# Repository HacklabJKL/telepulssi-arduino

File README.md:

<!-- -*- mode: markdown; -*- -->
# Telepulssi TP-KN10 driver for Arduino

Local radio amateur club OH6AD has "bonked" some 80s display modules
built by Telepulssi Oy. [Zouppen](https://twitter.com/zouppen) and
kahvikello accepted the challenge of reverse engineering them to
display animations via USB and developed this driver.

See [Youtube video](https://www.youtube.com/watch?v=fZEshGM8jz8) of
the screen in action.

## Building

Open Arduino IDE and build [avr.ino](avr/avr.ino). Supported
microcontrollers include all ATMega328 and ATMega32u4 models. Can
easily ported to other MCUs. Change pin definitions in the source if
your hardware is different from ours.

To see how to wire TP-KN10 to Arduino, see [pinout](pinout.md).

## Processing

[Processing](https://processing.org/) is the most fun way to control
Telepulssi. Processing version 3.3 or newer is recommended.

Open
[processing/hello/hello.pde](processing/hello/hello.pde)
to Processing, change serial port name, hack and run! :-)

Also, it has Telepulssi emulator!

## UDP interface

When running UDP interface, first set serial port settings (replace
serial port to match yours):

```sh
stty -F /dev/ttyACM0 raw 19200
```

### Start UDP server

```sh
cd tools
runghc UdpServer.hs >/dev/ttyACM0
```

TODO: Make Cabal package for UdpServer to make it run more easily.

### Send PNG images

Send any image over UDP port to this screen by running:

```sh
nc -uw0 SERVER_IP 1337 <your_image.png
```

### Naïve clock

```sh
./effects/clock /dev/ttyUSB0
```

## Missing features

1. Cabal package for UDP server
1. Schematics

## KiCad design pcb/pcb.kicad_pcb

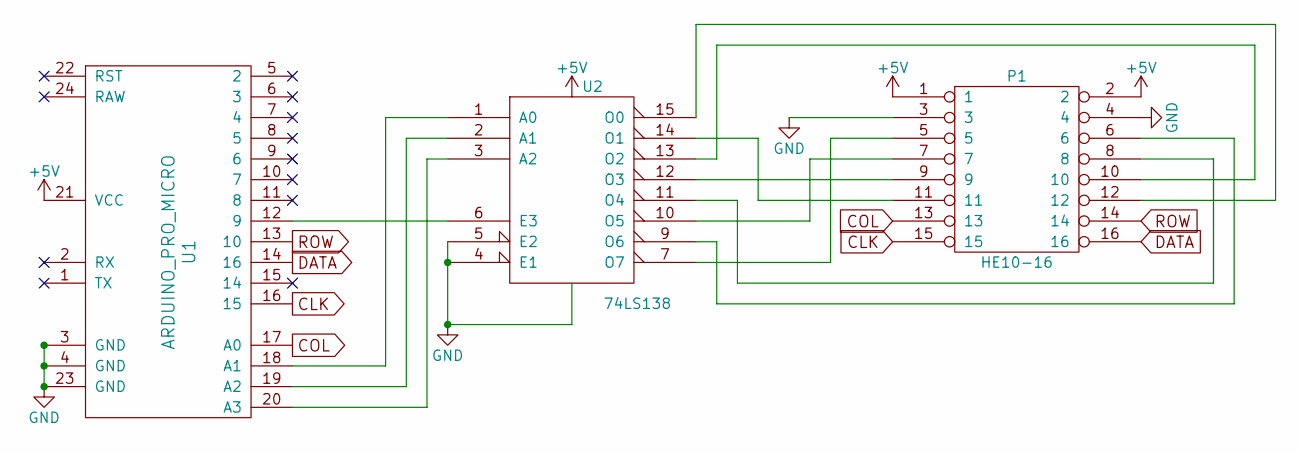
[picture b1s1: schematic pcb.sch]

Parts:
P1: HE10-16; IDC_Header_Straight_16pins
U1: ARDUINO_PRO_MICRO
U2: 74LS138; DIP-16_W7.62mm

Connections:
+5V: P1.1, P1.2, U1.21 (VCC), U2.16 (VCC)
CLK: P1.15, U1.16 (15)
COL: P1.13, U1.17 (A0)
DATA: P1.16, U1.14 (16)
GND: P1.3, P1.4, U1.3 (GND), U1.4 (GND), U1.23 (GND), U2.4 (E1), U2.5 (E2), U2.8 (GND)
unnamed: P1.5, U2.7 (O7)
unnamed: P1.6, U2.9 (O6)
unnamed: P1.7, U2.10 (O5)
unnamed: P1.8, U2.11 (O4)
unnamed: P1.9, U2.12 (O3)
unnamed: P1.10, U2.13 (O2)
unnamed: P1.11, U2.14 (O1)
unnamed: P1.12, U2.15 (O0)
unnamed: U1.12 (9), U2.6 (E3)
unnamed: U1.18 (A1), U2.1 (A0)
unnamed: U1.19 (A2), U2.2 (A1)
unnamed: U1.20 (A3), U2.3 (A2)
ROW: P1.14, U1.13 (10)

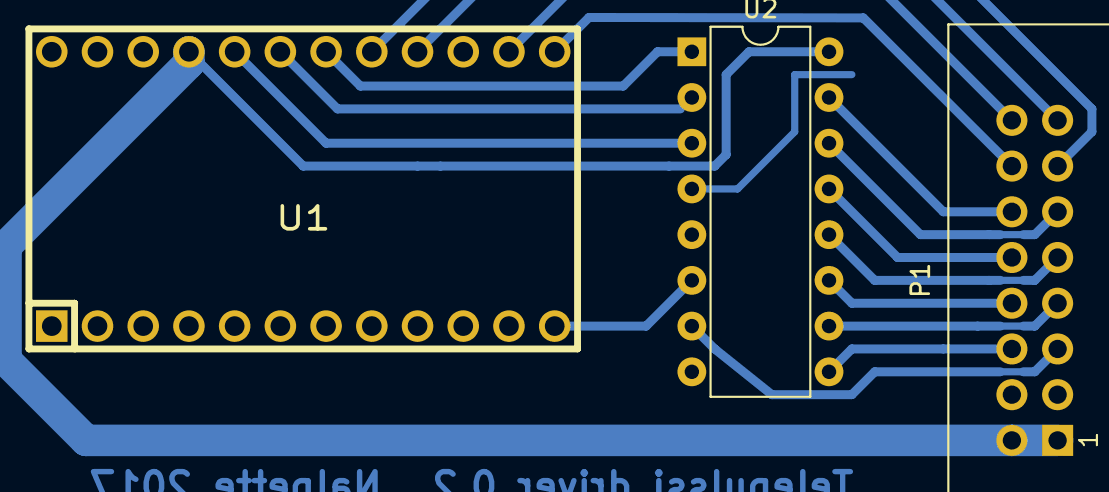
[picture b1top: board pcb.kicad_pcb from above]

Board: 2 copper layers, 3 parts (0 on the bottom side), 18 nets.

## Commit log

2017-01-29 Show preliminary pinout for Arduino
2017-01-31 Initial version of the display driver rendering static bitmap
2017-01-31 Optimize display driving by minimizing time spent when screen is off
2017-01-31 Use interrupts for display driving
2017-01-31 Read frames from serial port. Uses single buffering only.
2017-01-31 Show text "hacklab.jkl" at boot
2017-01-31 Add some examples of driving the display
2017-01-31 Fix pinout typo
2017-01-31 Use double buffering (thanks for Elovalo project)
2017-01-31 Update README.md ingress and add some examples.
2017-01-31 Markup fix
2017-02-01 Add bitcoin ticker initial version (rendering to file)
2017-02-01 Make the bitcoin ticker great again!
2017-02-01 Show rate movements with an arrow
2017-02-01 Reorganize files
2017-02-01 bugfix: Highest possible screen value is 0x1F, not 0x20
2017-02-01 Speed up refresh rate from 89 Hz to 1/(150e-6*8*7) Hz = 119 Hz
2017-02-01 Make the AVR code mode readable by adding comments and organizing a bit
2017-02-01 Add some example effects
2017-02-02 Simplify and document fade-in renderer
    Simplify text rendering arguments by removing unnecessary ImageMagick
    parameters and move some common tricks like splicing the output to a
    variable.
2017-02-02 Move common parts of text rendering to common.sh
2017-02-02 Fix bug in serial port settings in send_frame
2017-02-02 send_frame: Use common.sh and synchronize screen first
2017-02-02 Use send_to_screen instead of custom serial handler
2017-02-02 Move shell script effects to effects/ subdirectory
2017-03-04 First hacky version of IRC printer
2017-04-15 Fix buffer swapping bug which caused tearing
2017-04-15 More speed – LISÄÄ VAUHTIA!
2017-04-16 Add example for Processing
2017-04-16 Fix examples to use new baud rate and fit Bitcoin ticker correctly
2017-04-16 Implement 4-intensity PWMx
2017-07-28 Grayscale image to 2-bit binary data converter tool
2017-07-29 Clean-up 2-bit grayscale generator and add serial command
2017-07-30 Initial version of 2-bit PWM encoder
2017-07-30 PWM decoder for text console
2017-07-30 Grayscale support for AVR
2017-07-30 Support ping command
2017-07-30 More steep curve to PWM
2017-07-30 Revert processing software PWM
    This reverts commit d7b51eb746abc733e6d72a2d8e2b3e2d3b690964.
2017-07-31 Add support for grayscale in Processing lib
2017-07-31 Lengthen PWM cycle 0 duration to make grayscale great again
2017-07-31 Tackle ghosts by changing the order of columns being drawn
2017-07-31 Make it more portable across different Arduinos
2017-07-31 Driver is portable except SPDR register which is an optimization
2017-08-01 Reduce flicker of 67% gray value
2017-08-01 Naive version of variable-run-length PWM
2017-08-01 Use Timer1 without Arduino lib to fine-tune timing
    PWM cycle timing starts after screen turn-on, so timing is more accurate
2017-08-02 Revert "Tackle ghosts by changing the order of columns being drawn"
    This reverts commit 88b75d278bf530128c2831c9e57fdd67b3e9ae60.
2017-08-02 Switch iterating order in the LED screen to reduce blanking.
    New order:
    1. PWM planes of a single LED segment row
    2. Segments rows from left to right
    3. Rows
    4. Flip frame, if available, otherwise; repeat.
2017-08-03 Subs for Assembly 2017 show
2017-08-04 Split Telepulssi encoder to multiple files
2017-08-04 Change telepulssify function from Monad to Either
2017-08-04 Add UDP interface
2017-08-04 Fix clock example
2017-08-04 Use Pro Micro pins instead of Duemilanove pins
2017-08-04 Fix links
2017-08-04 Update pinout
2017-08-04 Use bottom of the window as a preview window
2017-08-04 Processing: Split serial traffic lib from the main .pde file
2017-08-05 Clean-up serial code, put it to a class and add EMULATOR! \o/
2017-08-05 Fix real-hardware-only mode
2017-08-09 Fix too low framerate issue
2017-08-18 Use PWM pin to disable output after PWM cycle length reached
2017-08-18 Split interrupt handler to multiple parts to allow using SPI interrupts later
2017-08-18 Clean-up and improve comments
2017-08-18 Pins of the final PCB
2017-08-18 Use SPI interrupts to drive the screen on after row change
2017-08-18 Some clean-ups in firmware. Make ROW_LATCH toggle time longer.
2017-08-18 Bugfix: Latched the data too early which broke grayscale.
2017-08-18 Start using smaller clock divider for extra refresh rate
    We also start using better-looking values which give us 102Hz refresh
    rate.
2017-08-18 Add support for setting PWM cycle lengths from the command line
    It adds support for firmware to set 16-bit unsigned run lengths and a
    command line tool for manipulating such numbers.
2017-08-18 Fix timing issue with SPI
    Stay blank until SPI transmission is ready and drive screen when both
    SPI and timer interrupts have arrived.
2017-08-18 Final tweaks
2017-08-18 Fix glitch in number gradient
    Drawing one rectangle starting from the middle of vertical row so it
    makes a smooth gradient when matrices are used in drawing.
2017-08-18 Draw Etteplan logo and clock in rotating fashion
2017-08-18 Switch the digit rotating direction
2017-08-18 Reorganize Processing examples directory
2017-08-18 Add font and do some cleanup
2017-08-18 Use matrix transformations to draw moving text. Makes it smoother.
2017-08-18 Prototype of a clock
2017-08-18 Change font. Make logo and font monochrome but scroll it smooth
2017-08-18 Blink more often
2017-08-18 Get serial port from command line if not emulating
2017-08-18 Less pixelated logo when moving. Use 2x resolution before scaling
2017-08-18 Draw day of week also
2017-08-29 Put formatting to a separate function
2017-09-05 Add schematics and PCB
2019-09-06 Temperature from weather.jyu.fi
